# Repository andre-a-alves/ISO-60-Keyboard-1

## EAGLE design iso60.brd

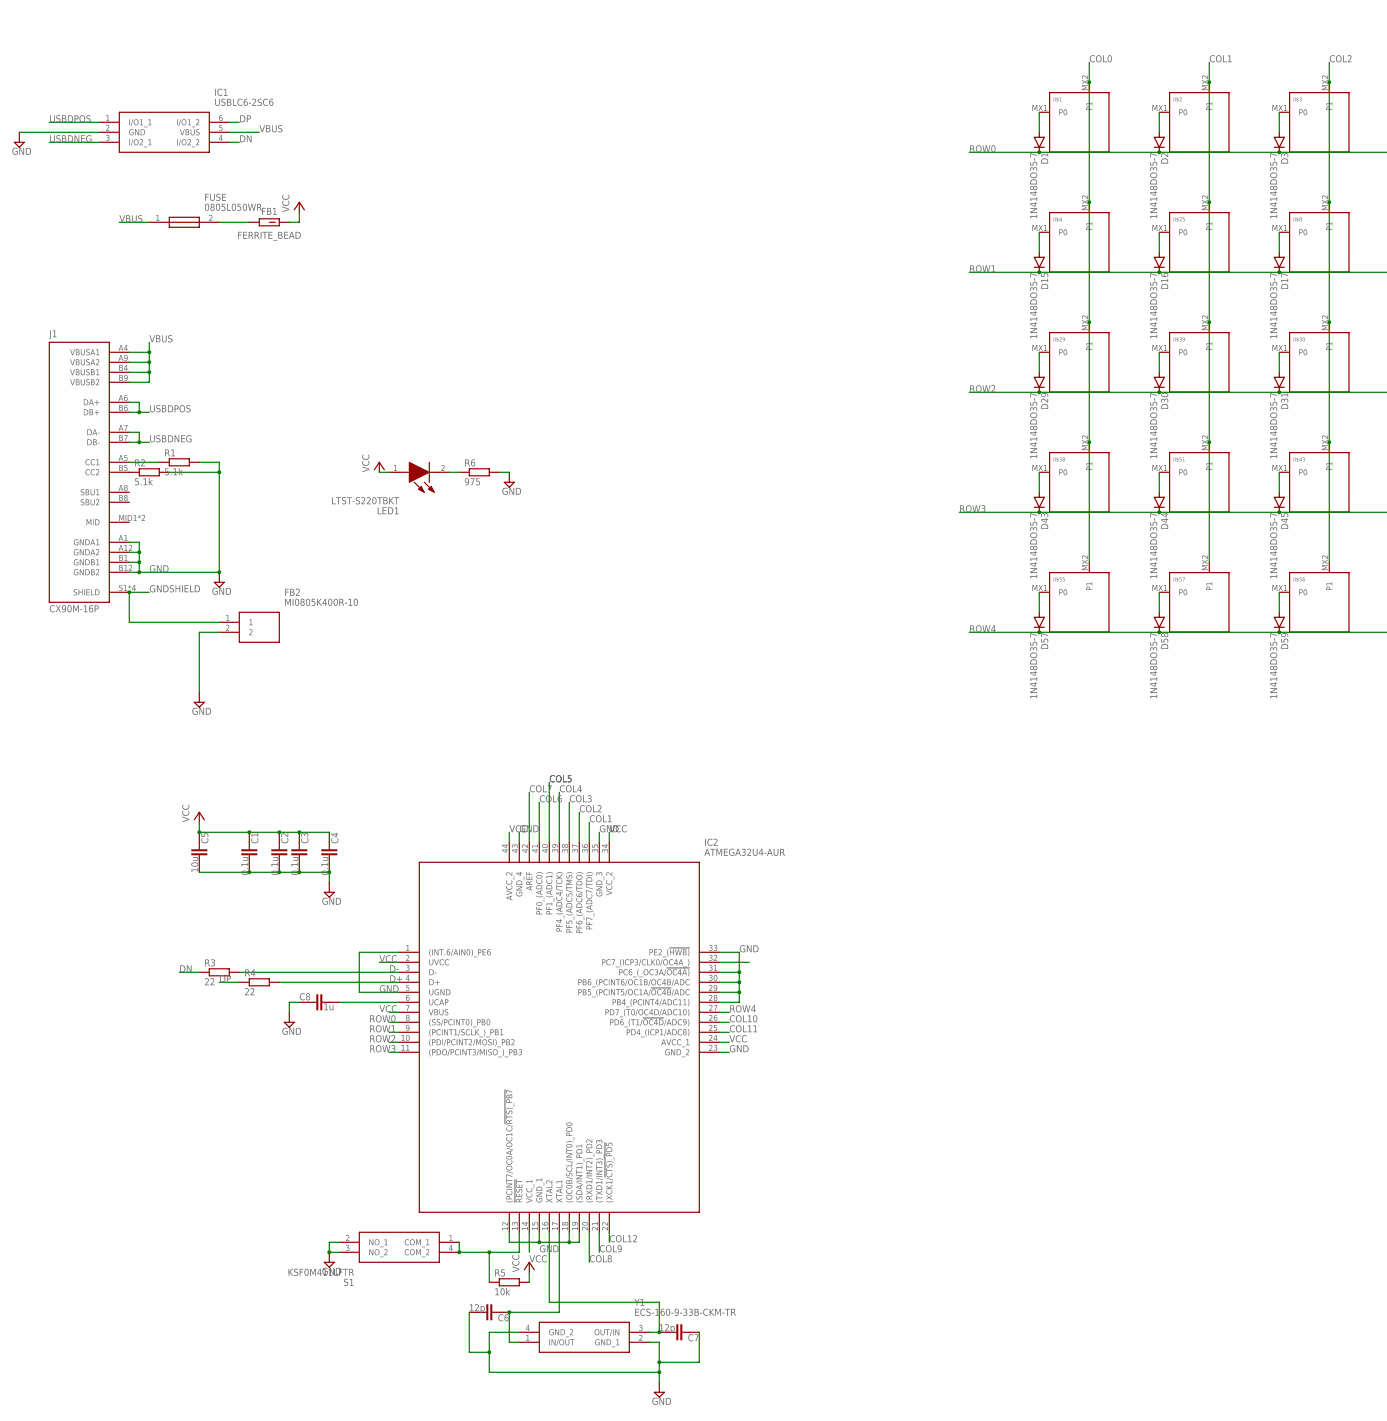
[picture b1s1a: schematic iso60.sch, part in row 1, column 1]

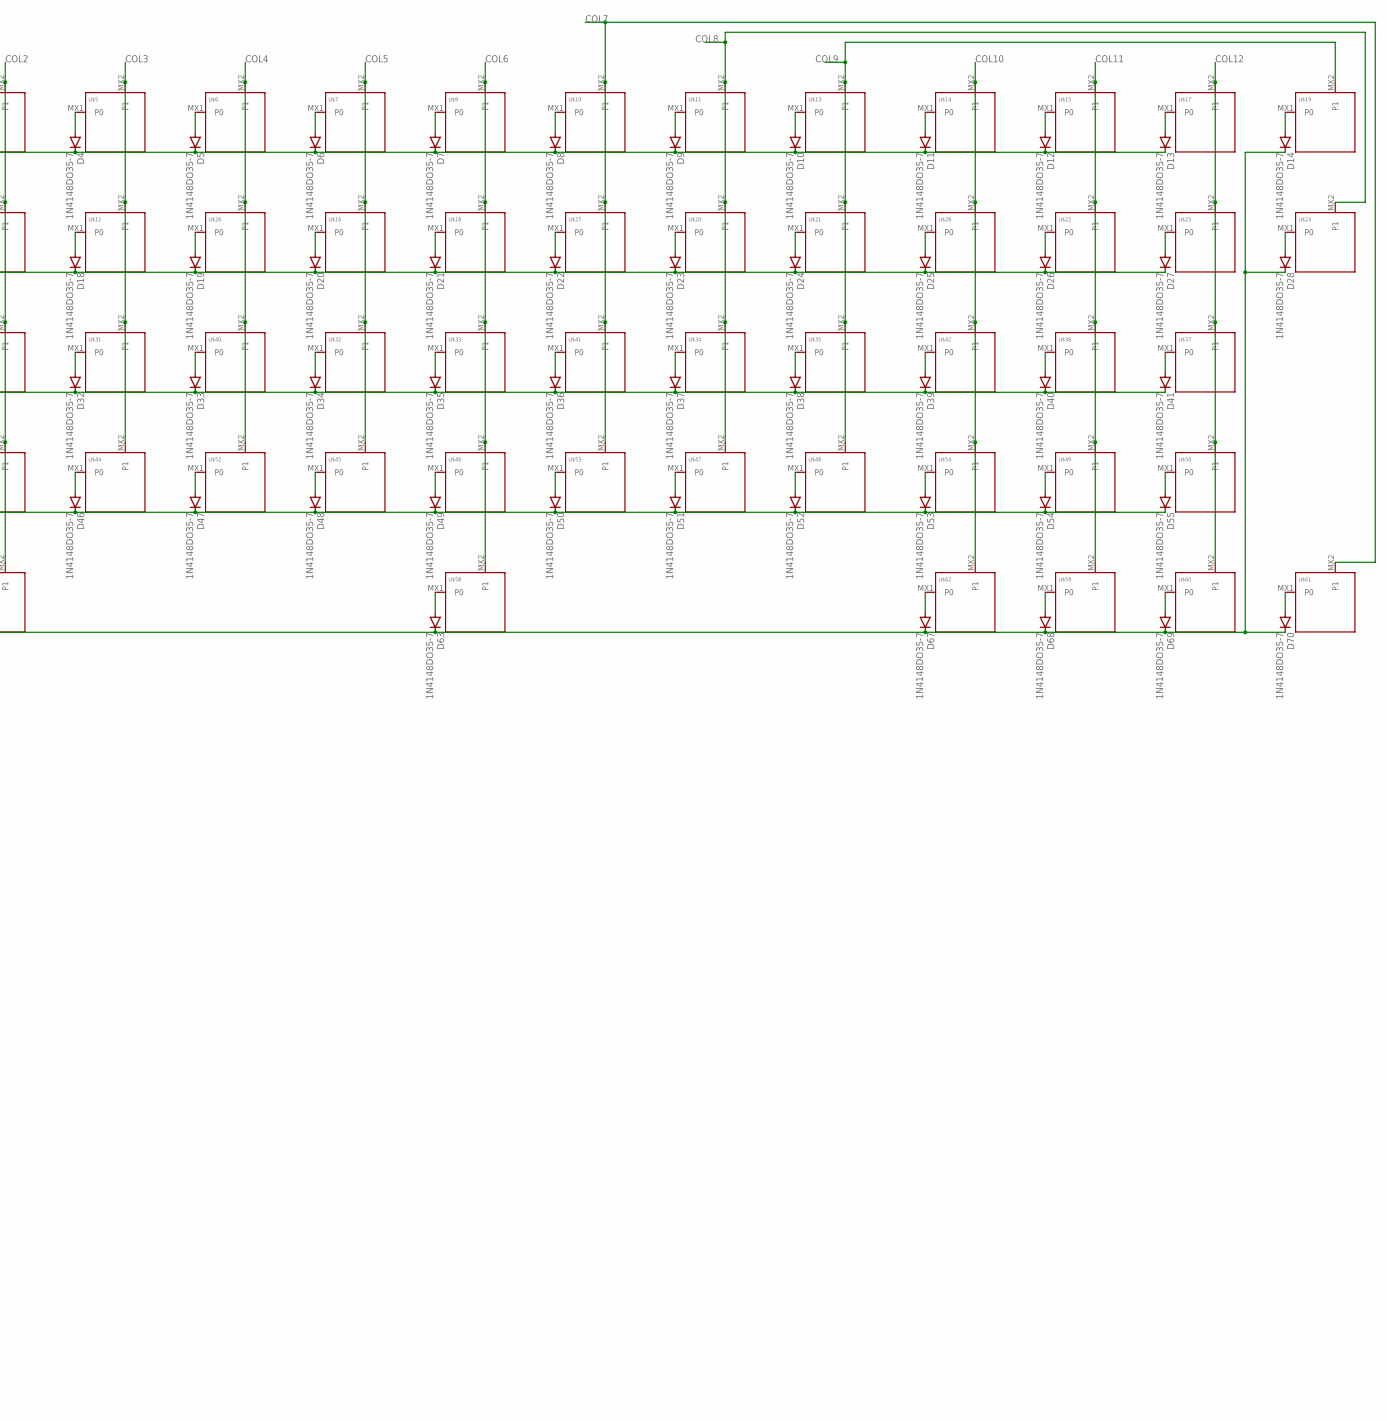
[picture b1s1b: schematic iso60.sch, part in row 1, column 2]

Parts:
C1, C2, C3, C4: 0.1u; C0805
C5: 10u; C0805
C6, C7: 12p; C0805
C8: 1u; C0805
D1, D2, D3, D4, D5, D6, D7, D8, D9, D10, D11, D12, D13, D14, D15, D16, D17, D18, D19, D20, D21, D22, D23, D24, D25, D26, D27, D28, D29, D30, D31, D32, D33, D34, D35, D36, D37, D38, D39, D40, D41, D43, D44, D45, D46, D47, D48, D49, D50, D51, D52, D53, D54, D55, D57, D58, D59, D63, D67, D68, D69, D70: 1N4148DO35-7; DO35-7
FB1: FERRITE_BEAD; BEADC2012X105N
FB2: MI0805K400R-10; BEADC2012X110N
FUSE: 0805L050WR; FUSC2114X125N
IC1: USBLC6-2SC6; SOT95P280X145-6N
IC2: ATMEGA32U4-AUR; QFP80P1200X1200X120-44N
J1: CX90M-16P; HRS_CX90M-16P
LED1: LTST-S220TBKT; LTSTS220TBKT
R1, R2: 5.1k; R0805
R3, R4: 22; R0805
R5: 10k; R0805
R6: 975; R0805
S1: KSF0M411LFTR
U$1, U$2, U$3, U$4, U$5, U$6, U$7, U$8, U$9, U$10, U$11, U$12, U$13, U$14, U$15, U$16, U$17, U$18, U$19, U$20, U$21, U$22, U$23, U$24, U$25, U$26, U$27, U$28, U$29, U$30, U$31, U$32, U$33, U$34, U$35, U$36, U$37, U$38, U$39, U$40, U$41, U$42, U$43, U$44, U$45, U$46, U$47, U$48, U$49, U$50, U$51, U$52, U$53, U$54, U$55, U$56, U$57, U$58, U$59, U$60, U$61, U$62: KEYSWITCH-PLAIN-MXHS-1U; MXHS-1U
Y1: ECS-160-9-33B-CKM-TR; ECS2501033BCKMTR

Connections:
COL0: IC2.32 (PC7_(ICP3/CLK0/OC4A_)), U$1.MX2 (P1), U$4.MX2 (P1), U$29.MX2 (P1), U$38.MX2 (P1), U$55.MX2 (P1)
COL1: IC2.36 (PF7_(ADC7/TDI)), U$2.MX2 (P1), U$25.MX2 (P1), U$39.MX2 (P1), U$51.MX2 (P1), U$57.MX2 (P1)
COL2: IC2.37 (PF6_(ADC6/TDO)), U$3.MX2 (P1), U$8.MX2 (P1), U$30.MX2 (P1), U$43.MX2 (P1), U$56.MX2 (P1)
COL3: IC2.38 (PF5_(ADC5/TMS)), U$5.MX2 (P1), U$12.MX2 (P1), U$31.MX2 (P1), U$44.MX2 (P1)
COL4: IC2.39 (PF4_(ADC4/TCK)), U$6.MX2 (P1), U$26.MX2 (P1), U$40.MX2 (P1), U$52.MX2 (P1)
COL5: IC2.40 (PF1_(ADC1)), U$7.MX2 (P1), U$16.MX2 (P1), U$32.MX2 (P1), U$45.MX2 (P1)
COL6: IC2.41 (PF0_(ADC0)), U$9.MX2 (P1), U$18.MX2 (P1), U$33.MX2 (P1), U$46.MX2 (P1), U$58.MX2 (P1)
COL7: IC2.42 (AREF), U$10.MX2 (P1), U$27.MX2 (P1), U$41.MX2 (P1), U$53.MX2 (P1), U$61.MX2 (P1)
COL8: IC2.20 ((RXD1/INT2)_PD2), U$11.MX2 (P1), U$20.MX2 (P1), U$24.MX2 (P1), U$34.MX2 (P1), U$47.MX2 (P1)
COL9: IC2.21 ((TXD1/INT3)_PD3), U$13.MX2 (P1), U$19.MX2 (P1), U$21.MX2 (P1), U$35.MX2 (P1), U$48.MX2 (P1)
COL10: IC2.26 (PD6_(T1/!OC4D!/ADC9)), U$14.MX2 (P1), U$28.MX2 (P1), U$42.MX2 (P1), U$54.MX2 (P1), U$62.MX2 (P1)
COL11: IC2.25 (PD4_(ICP1/ADC8)), U$15.MX2 (P1), U$22.MX2 (P1), U$36.MX2 (P1), U$49.MX2 (P1), U$59.MX2 (P1)
COL12: IC2.22 ((XCK1/!CTS)_PD5), U$17.MX2 (P1), U$23.MX2 (P1), U$37.MX2 (P1), U$50.MX2 (P1), U$60.MX2 (P1)
D+: IC2.4 (D+), R4.2
D-: IC2.3 (D-), R3.2
DN: IC1.4 (I/O2_2), R3.1
DP: IC1.6 (I/O1_2), R4.1
GND: C1.2, C2.2, C3.2, C4.2, C5.2, C6.2, C7.1, C8.1, FB2.2, IC1.2 (GND), IC2.1 ((INT.6/AIN0)_PE6), IC2.5 (UGND), IC2.12 ((PCINT7/OC0A/OC1C/!RTS)_PB7), IC2.15 (GND_1), IC2.18 ((OC0B/SCL/INT0)_PD0), IC2.19 ((SDA/INT1)_PD1), IC2.23 (GND_2), IC2.28 (PB4_(PCINT4/ADC11)), IC2.29 (PB5_(PCINT5/OC1A/!OC4B!/ADC), IC2.30 (PB6_(PCINT6/OC1B/OC4B/ADC), IC2.31 (PC6_(_OC3A/!OC4A)), IC2.33 (PE2_(!HWB)), IC2.35 (GND_3), IC2.43 (GND_4), J1.A1 (GNDA1), J1.A12 (GNDA2), J1.B1 (GNDB1), J1.B12 (GNDB2), R1.2, R2.2, R6.2, S1.2 (NO_1), S1.3 (NO_2), Y1.2 (GND_1), Y1.4 (GND_2)
GNDSHIELD: FB2.1, J1.S1 (SHIELD), J1.S2 (SHIELD), J1.S3 (SHIELD), J1.S4 (SHIELD)
unnamed: D1.A, U$1.MX1 (P0)
unnamed: D2.A, U$2.MX1 (P0)
unnamed: D3.A, U$3.MX1 (P0)
unnamed: D4.A, U$5.MX1 (P0)
unnamed: D5.A, U$6.MX1 (P0)
unnamed: D6.A, U$7.MX1 (P0)
unnamed: D7.A, U$9.MX1 (P0)
unnamed: D8.A, U$10.MX1 (P0)
unnamed: D9.A, U$11.MX1 (P0)
unnamed: D10.A, U$13.MX1 (P0)
unnamed: D11.A, U$14.MX1 (P0)
unnamed: D12.A, U$15.MX1 (P0)
unnamed: D13.A, U$17.MX1 (P0)
unnamed: D14.A, U$19.MX1 (P0)
unnamed: D15.A, U$4.MX1 (P0)
unnamed: D16.A, U$25.MX1 (P0)
unnamed: D17.A, U$8.MX1 (P0)
unnamed: D18.A, U$12.MX1 (P0)
unnamed: D19.A, U$26.MX1 (P0)
unnamed: D20.A, U$16.MX1 (P0)
unnamed: D21.A, U$18.MX1 (P0)
unnamed: D22.A, U$27.MX1 (P0)
unnamed: D23.A, U$20.MX1 (P0)
unnamed: D24.A, U$21.MX1 (P0)
unnamed: D25.A, U$28.MX1 (P0)
unnamed: D26.A, U$22.MX1 (P0)
unnamed: D27.A, U$23.MX1 (P0)
unnamed: D28.A, U$24.MX1 (P0)
unnamed: D29.A, U$29.MX1 (P0)
unnamed: D30.A, U$39.MX1 (P0)
unnamed: D31.A, U$30.MX1 (P0)
unnamed: D32.A, U$31.MX1 (P0)
unnamed: D33.A, U$40.MX1 (P0)
unnamed: D34.A, U$32.MX1 (P0)
unnamed: D35.A, U$33.MX1 (P0)
unnamed: D36.A, U$41.MX1 (P0)
unnamed: D37.A, U$34.MX1 (P0)
unnamed: D38.A, U$35.MX1 (P0)
unnamed: D39.A, U$42.MX1 (P0)
unnamed: D40.A, U$36.MX1 (P0)
unnamed: D41.A, U$37.MX1 (P0)
unnamed: D43.A, U$38.MX1 (P0)
unnamed: D44.A, U$51.MX1 (P0)
unnamed: D45.A, U$43.MX1 (P0)
unnamed: D46.A, U$44.MX1 (P0)
unnamed: D47.A, U$52.MX1 (P0)
unnamed: D48.A, U$45.MX1 (P0)
unnamed: D49.A, U$46.MX1 (P0)
unnamed: D50.A, U$53.MX1 (P0)
unnamed: D51.A, U$47.MX1 (P0)
unnamed: D52.A, U$48.MX1 (P0)
unnamed: D53.A, U$54.MX1 (P0)
unnamed: D54.A, U$49.MX1 (P0)
unnamed: D55.A, U$50.MX1 (P0)
unnamed: D57.A, U$55.MX1 (P0)
unnamed: D58.A, U$57.MX1 (P0)
unnamed: D59.A, U$56.MX1 (P0)
unnamed: D63.A, U$58.MX1 (P0)
unnamed: D67.A, U$62.MX1 (P0)
unnamed: D68.A, U$59.MX1 (P0)
unnamed: D69.A, U$60.MX1 (P0)
unnamed: D70.A, U$61.MX1 (P0)
unnamed: LED1.2 (K), R6.1
unnamed: J1.A5 (CC1), R1.1
unnamed: J1.B5 (CC2), R2.1
unnamed: FB1.1, FUSE.2
unnamed: C6.1, IC2.17 (XTAL1), Y1.1 (IN/OUT)
unnamed: C7.2, IC2.16 (XTAL2), Y1.3 (OUT/IN)
unnamed: C8.2, IC2.6 (UCAP)
unnamed: IC2.13 (!RESET), R5.1, S1.1 (COM_1), S1.4 (COM_2)
ROW0: D1.C, D2.C, D3.C, D4.C, D5.C, D6.C, D7.C, D8.C, D9.C, D10.C, D11.C, D12.C, D13.C, IC2.8 ((SS/PCINT0)_PB0)
ROW1: D15.C, D16.C, D17.C, D18.C, D19.C, D20.C, D21.C, D22.C, D23.C, D24.C, D25.C, D26.C, D27.C, IC2.9 ((PCINT1/SCLK_)_PB1)
ROW2: D29.C, D30.C, D31.C, D32.C, D33.C, D34.C, D35.C, D36.C, D37.C, D38.C, D39.C, D40.C, D41.C, IC2.10 ((PDI/PCINT2/MOSI)_PB2)
ROW3: D43.C, D44.C, D45.C, D46.C, D47.C, D48.C, D49.C, D50.C, D51.C, D52.C, D53.C, D54.C, D55.C, IC2.11 ((PDO/PCINT3/MISO_)_PB3)
ROW4: D14.C, D28.C, D57.C, D58.C, D59.C, D63.C, D67.C, D68.C, D69.C, D70.C, IC2.27 (PD7_(T0/OC4D/ADC10))
USBDNEG: IC1.3 (I/O2_1), J1.A7 (DA-), J1.B7 (DB-)
USBDPOS: IC1.1 (I/O1_1), J1.A6 (DA+), J1.B6 (DB+)
VBUS: FUSE.1, IC1.5 (VBUS), J1.A4 (VBUSA1), J1.A9 (VBUSA2), J1.B4 (VBUSB1), J1.B9 (VBUSB2)
VCC: C1.1, C2.1, C3.1, C4.1, C5.1, FB1.2, IC2.2 (UVCC), IC2.7 (VBUS), IC2.14 (VCC_1), IC2.24 (AVCC_1), IC2.34 (VCC_2), IC2.44 (AVCC_2), LED1.1 (A), R5.2

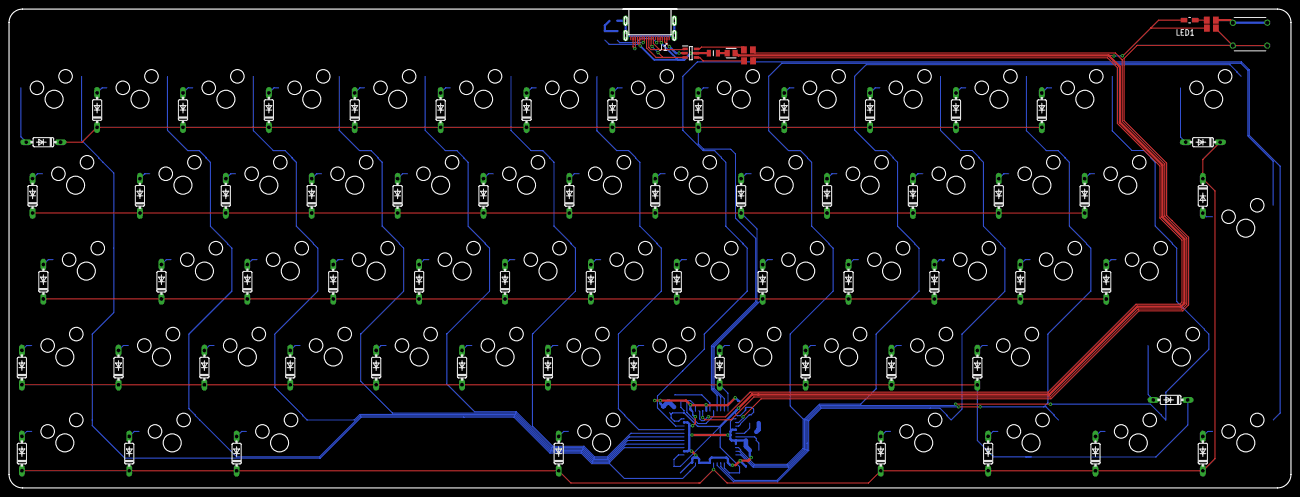
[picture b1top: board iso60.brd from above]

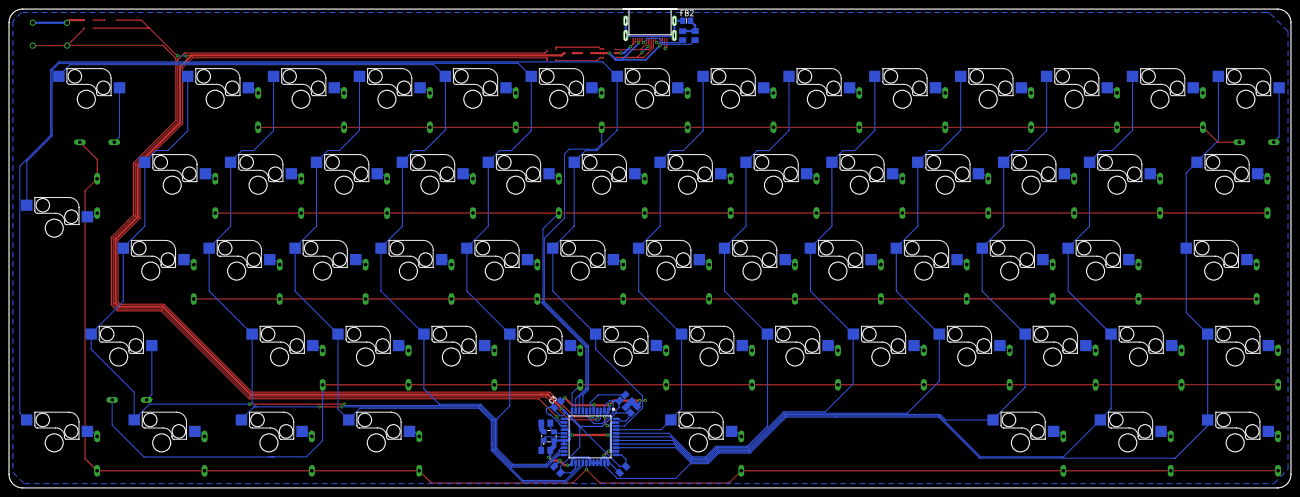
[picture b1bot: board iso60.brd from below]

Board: 2 copper layers, 284.3 x 106.2 mm, 147 parts (75 on the bottom side), 98 nets.
